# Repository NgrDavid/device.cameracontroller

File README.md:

## Harp Camera Trigger Control

This device allows to trigger up to 2 cameras at a predefined frequency pulse or 2 servo motors. Connect cameras to CAM0 TRIG and CAM1 TRIG ports.

### Key Features ###

* Separate sample frequency for each camera
* Alternate between camera triggering and servo motor control
* Each camera output can be handled as pure digital output

### Connectivity ###

* 1x clock sync input (CLKIN) [stereo jack]
* 1x USB (for computer) [USB type B]
* 1x 5V supply out [screw terminal]
* 4x digital outputs (I/O interface for 2 cameras): CAM0 TRIG, CAM0 SYNC, CAM1 TRIG, CAM1 SYNC [screw terminal]
* 1x digital input for general purpose or camera control (IN0) [BNC]

## Interface ##

The interface with the Harp board can be done through [Bonsai](https://bonsai-rx.org/) or a dedicated GUI (Graphical User Interface).

In order to use this GUI, there are some software that needs to be installed:

1 - Install the [drivers](https://bitbucket.org/fchampalimaud/downloads/downloads/UsbDriver-2.12.26.zip).

2 - Install the [runtime](https://bitbucket.org/fchampalimaud/downloads/downloads/Runtime-1.0.zip).

3 - Reboot the computer.

4 - Install the [GUI](https://bitbucket.org/fchampalimaud/downloads/downloads/Harp%20Camera%20Controller%20v1.0.1.zip).

## Licensing ##

Each subdirectory will contain a license or, possibly, a set of licenses if it involves both hardware and software.

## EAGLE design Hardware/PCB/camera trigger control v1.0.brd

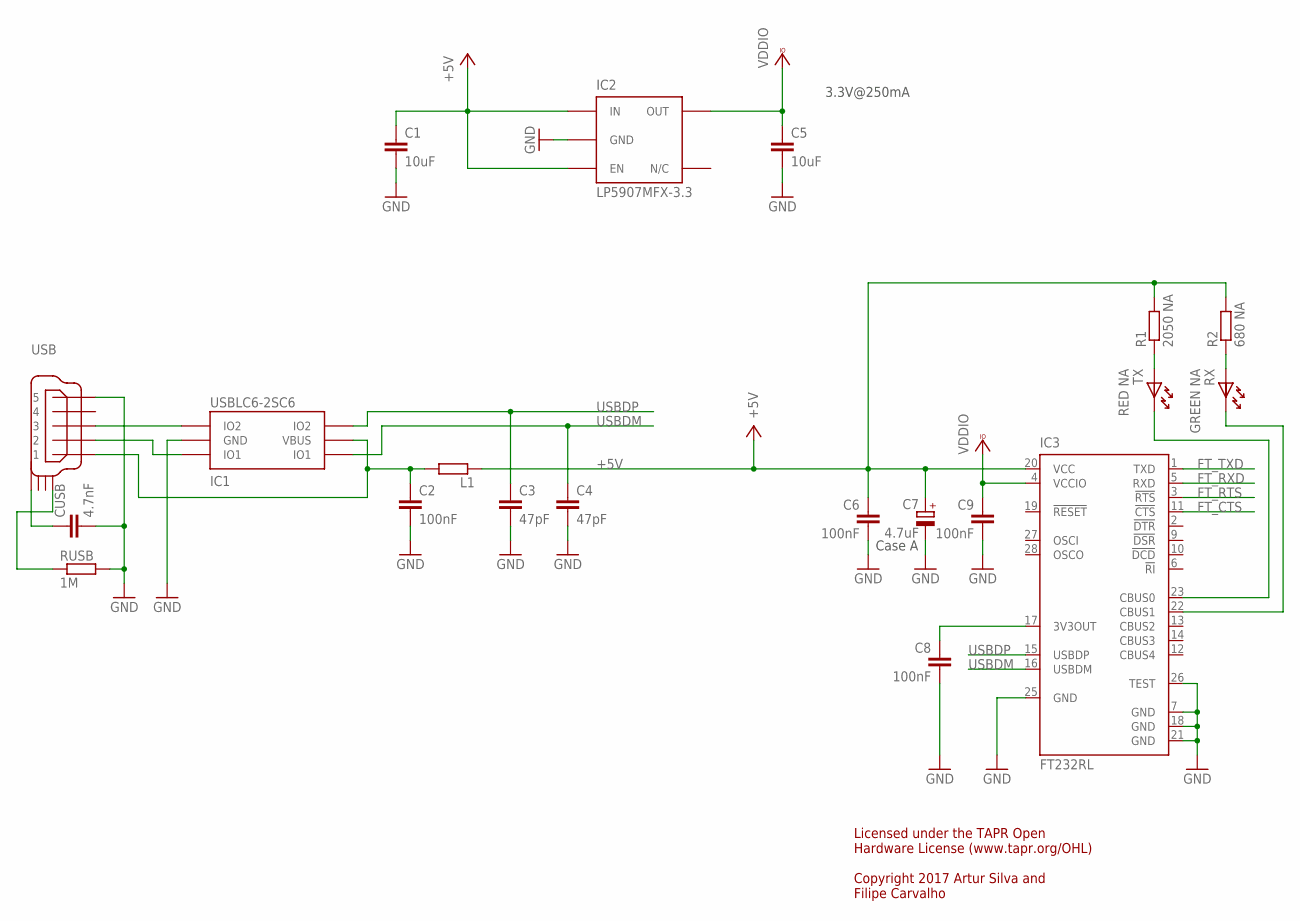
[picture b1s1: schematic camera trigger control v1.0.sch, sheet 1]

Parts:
C1, C5: 10uF; C0603
C2, C6, C8, C9: 100nF; C0402
C3, C4: 47pF; C0402
C7: 4.7uF; A/3216-18W
CUSB: 4.7nF; C0402
IC1: USBLC6-2SC6; SOT23-6L
IC2: LP5907MFX-3.3; TSOT23-5
IC3: FT232RL; SSOP28
L1: ???; R0805
R1: 2050 NA; R0402
R2: 680 NA; R0402
RUSB: 1M; R0402
RX: GREEN NA; LED_HAND
TX: RED NA; LED_HAND
USB: USB_MINI_B; 240-0002-1

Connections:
+5V: C1.1, C6.1, C7.+, IC2.1 (IN), IC2.3 (EN), IC3.20 (VCC), L1.1, R1.2, R2.2; also elsewhere on the board
FT_CTS: IC3.11 (!CTS); also elsewhere on the board
FT_RTS: IC3.3 (!RTS); also elsewhere on the board
FT_RXD: IC3.5 (RXD); also elsewhere on the board
FT_TXD: IC3.1 (TXD); also elsewhere on the board
GND: C1.2, C2.2, C3.2, C4.2, C5.2, C6.2, C7.-, C8.2, C9.2, CUSB.2, IC1.P$2 (GND), IC2.2 (GND), IC3.7 (GND), IC3.18 (GND), IC3.21 (GND), IC3.25 (GND), IC3.26 (TEST), RUSB.2, USB.P$5 (5); also elsewhere on the board
unnamed: C8.1, IC3.17 (3V3OUT)
unnamed: C2.1, IC1.P$5 (VBUS), L1.2, USB.P$1 (1)
unnamed: IC1.P$1 (IO1), USB.P$2 (2)
unnamed: R2.1, RX.A
unnamed: IC3.23 (CBUS0), TX.K
unnamed: IC3.22 (CBUS1), RX.K
unnamed: IC1.P$3 (IO2), USB.P$3 (3)
unnamed: CUSB.1, USB.SHIELD_4
unnamed: RUSB.1, USB.SHIELD_1
unnamed: R1.1, TX.A
USBDM: C4.1, IC1.P$6 (IO1), IC3.16 (USBDM)
USBDP: C3.1, IC1.P$4 (IO2), IC3.15 (USBDP)
VCCIO: C5.1, C9.1, IC2.5 (OUT), IC3.4 (VCCIO); also elsewhere on the board

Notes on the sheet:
Case A
3.3V@250mA
Licensed under the TAPR Open Hardware License (www.tapr.org/OHL) Copyright 2017 Artur Silva and Filipe Carvalho

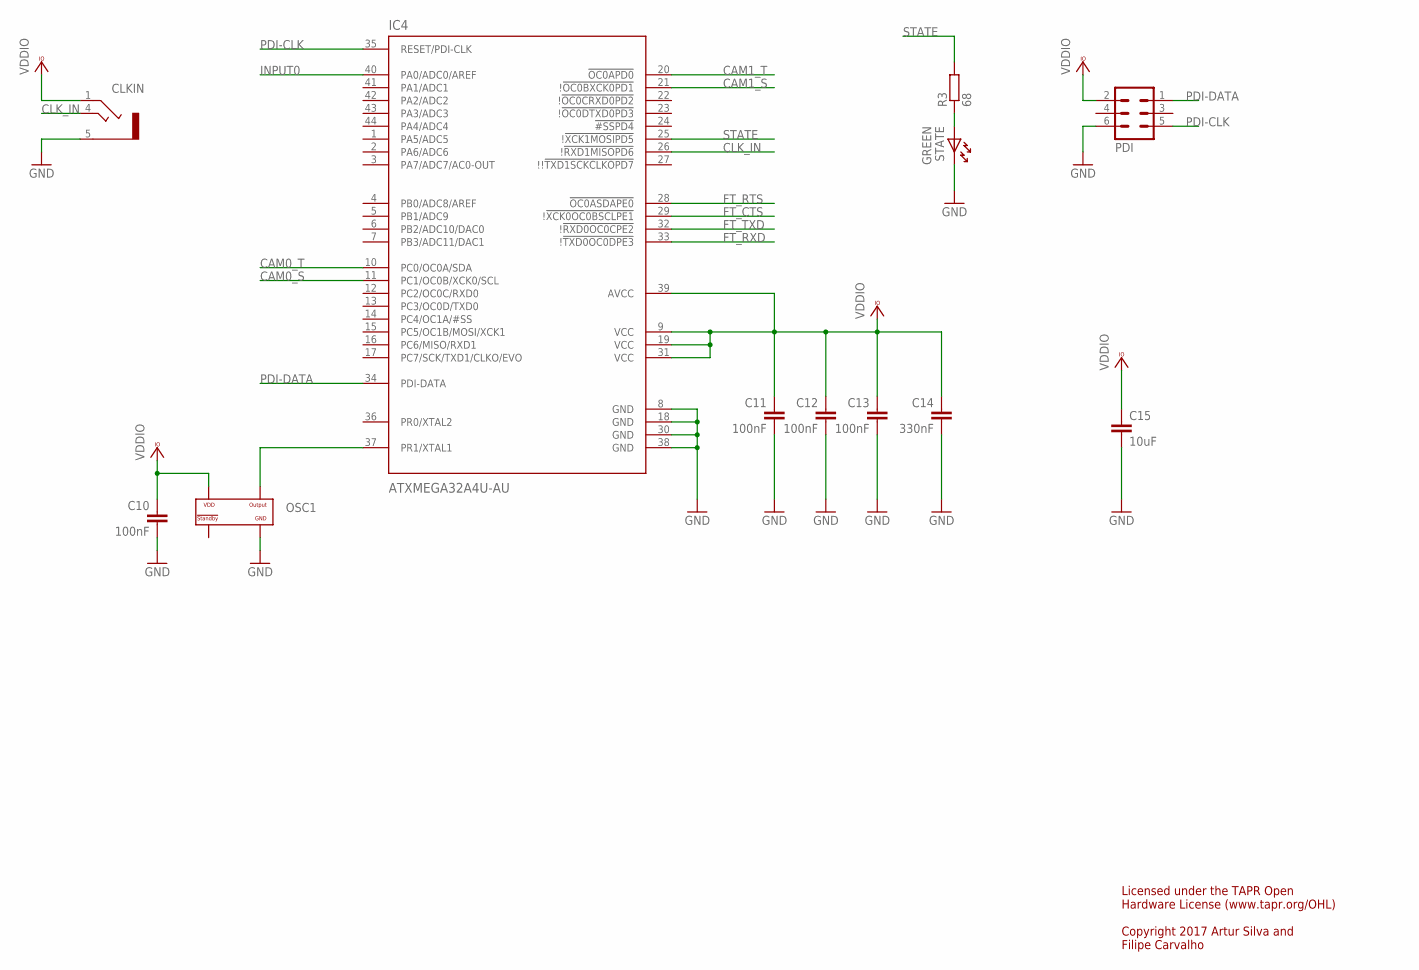
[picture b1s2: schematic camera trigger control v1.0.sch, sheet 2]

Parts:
C10, C11, C12, C13: 100nF; C0402
C14: 330nF; C0402
C15: 10uF; C0603
CLKIN: STEREO_JACK; 35RASMT2BHNTRX
IC4: ATXMEGA32A4U-AU; QFP80P1200X1200X120-44N
OSC1: OSCILLATOR; OSCILLATOR_3.2X2.5
PDI: MA03-2
R3: 68; R0402
STATE: GREEN; LED_HAND

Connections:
CAM0_S: IC4.11 (PC1/OC0B/XCK0/SCL); also elsewhere on the board
CAM0_T: IC4.10 (PC0/OC0A/SDA); also elsewhere on the board
CAM1_S: IC4.21 (!!OC0BXCK0PD1); also elsewhere on the board
CAM1_T: IC4.20 (!OC0APD0); also elsewhere on the board
CLK_IN: CLKIN.4, IC4.26 (!!RXD1MISOPD6)
FT_CTS: IC4.29 (!!XCK0OC0BSCLPE1); also elsewhere on the board
FT_RTS: IC4.28 (!OC0ASDAPE0); also elsewhere on the board
FT_RXD: IC4.33 (!!TXD0OC0DPE3); also elsewhere on the board
FT_TXD: IC4.32 (!!RXD0OC0CPE2); also elsewhere on the board
GND: C10.2, C11.2, C12.2, C13.2, C14.2, C15.2, CLKIN.5, IC4.8 (GND), IC4.18 (GND), IC4.30 (GND), IC4.38 (GND), OSC1.P$2 (GND), PDI.6, STATE.K; also elsewhere on the board
INPUT0: IC4.40 (PA0/ADC0/AREF); also elsewhere on the board
unnamed: R3.1, STATE.A
OSC1: IC4.37 (PR1/XTAL1), OSC1.P$3 (OUTPUT)
PDI-CLK: IC4.35 (RESET/PDI-CLK), PDI.5
PDI-DATA: IC4.34 (PDI-DATA), PDI.1
STATE: IC4.25 (!!XCK1MOSIPD5), R3.2
VCCIO: C10.1, C11.1, C12.1, C13.1, C14.1, C15.1, CLKIN.1, IC4.9 (VCC), IC4.19 (VCC), IC4.31 (VCC), IC4.39 (AVCC), OSC1.P$4 (VDD), PDI.2; also elsewhere on the board

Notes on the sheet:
Licensed under the TAPR Open Hardware License (www.tapr.org/OHL) Copyright 2017 Artur Silva and Filipe Carvalho

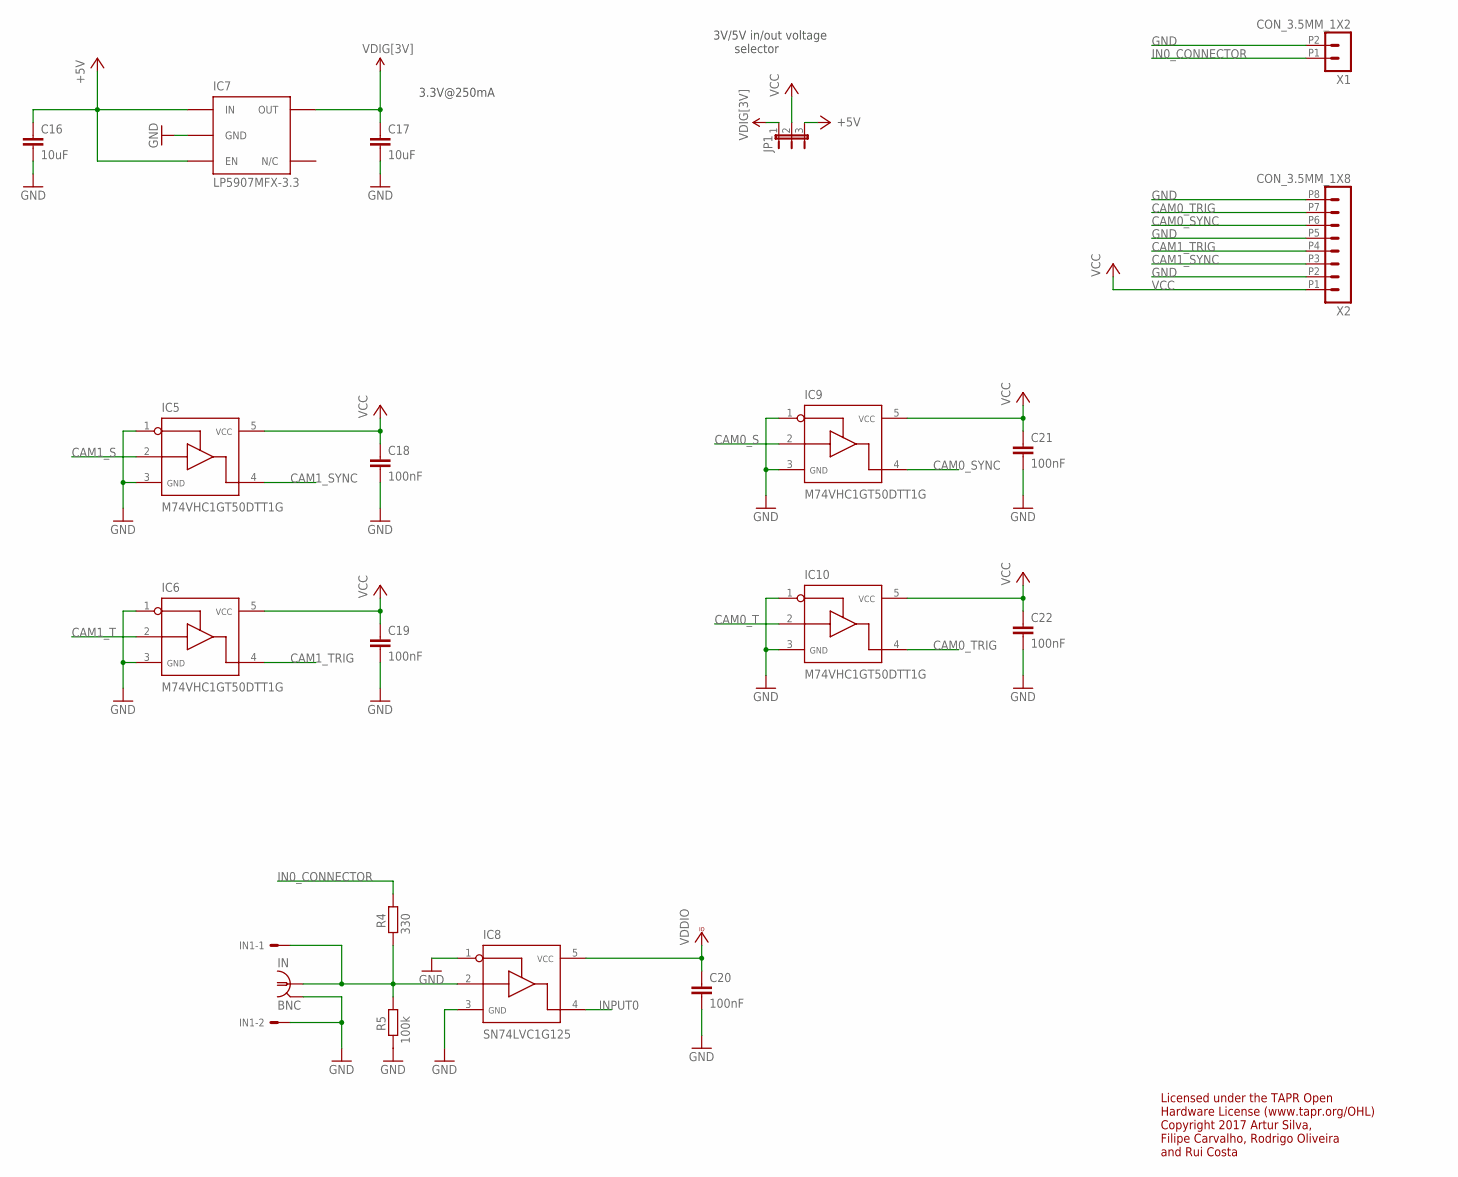
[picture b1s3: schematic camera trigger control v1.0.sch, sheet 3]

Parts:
C16, C17: 10uF; C0603
C18, C19, C20, C21, C22: 100nF; C0402
IC5, IC6, IC9, IC10: M74VHC1GT50DTT1G; SOT23-5
IC7: LP5907MFX-3.3; TSOT23-5
IC8: SN74LVC1G125; SOT23-5
IN: BNC; BNC_RA
IN1: 22-05-7028-02; 7395-02
JP1: JP2E; JP2
R4: 330; R0402
R5: 100k; R0402
X1: CON_3.5MM_1X2
X2: CON_3.5MM_1X8

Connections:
+5V: C16.1, IC7.1 (IN), IC7.3 (EN), JP1.3; also elsewhere on the board
CAM0_S: IC9.2; also elsewhere on the board
CAM0_SYNC: IC9.4, X2.P6 (6)
CAM0_T: IC10.2; also elsewhere on the board
CAM0_TRIG: IC10.4, X2.P7 (7)
CAM1_S: IC5.2; also elsewhere on the board
CAM1_SYNC: IC5.4, X2.P3 (3)
CAM1_T: IC6.2; also elsewhere on the board
CAM1_TRIG: IC6.4, X2.P4 (4)
GND: C16.2, C17.2, C18.2, C19.2, C20.2, C21.2, C22.2, IC5.1, IC5.3, IC6.1, IC6.3, IC7.2 (GND), IC8.1, IC8.3, IC9.1, IC9.3, IC10.1, IC10.3, IN.2, IN1.2, R5.2, X1.P2 (2), X2.P2 (2), X2.P5 (5), X2.P8 (8); also elsewhere on the board
IN0: IC8.2, IN.1, IN1.1, R4.2, R5.1
IN0_CONNECTOR: R4.1, X1.P1 (1)
INPUT0: IC8.4; also elsewhere on the board
VCC: C18.1, C19.1, C21.1, C22.1, IC5.5, IC6.5, IC9.5, IC10.5, JP1.2, X2.P1 (1)
VCCIO: C20.1, IC8.5; also elsewhere on the board
VDIG[3V]: C17.1, IC7.5 (OUT), JP1.1

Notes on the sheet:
3.3V@250mA
3V/5V in/out voltage selector
Licensed under the TAPR Open Hardware License (www.tapr.org/OHL) Copyright 2017 Artur Silva, Filipe Carvalho, Rodrigo Oliveira and Rui Costa

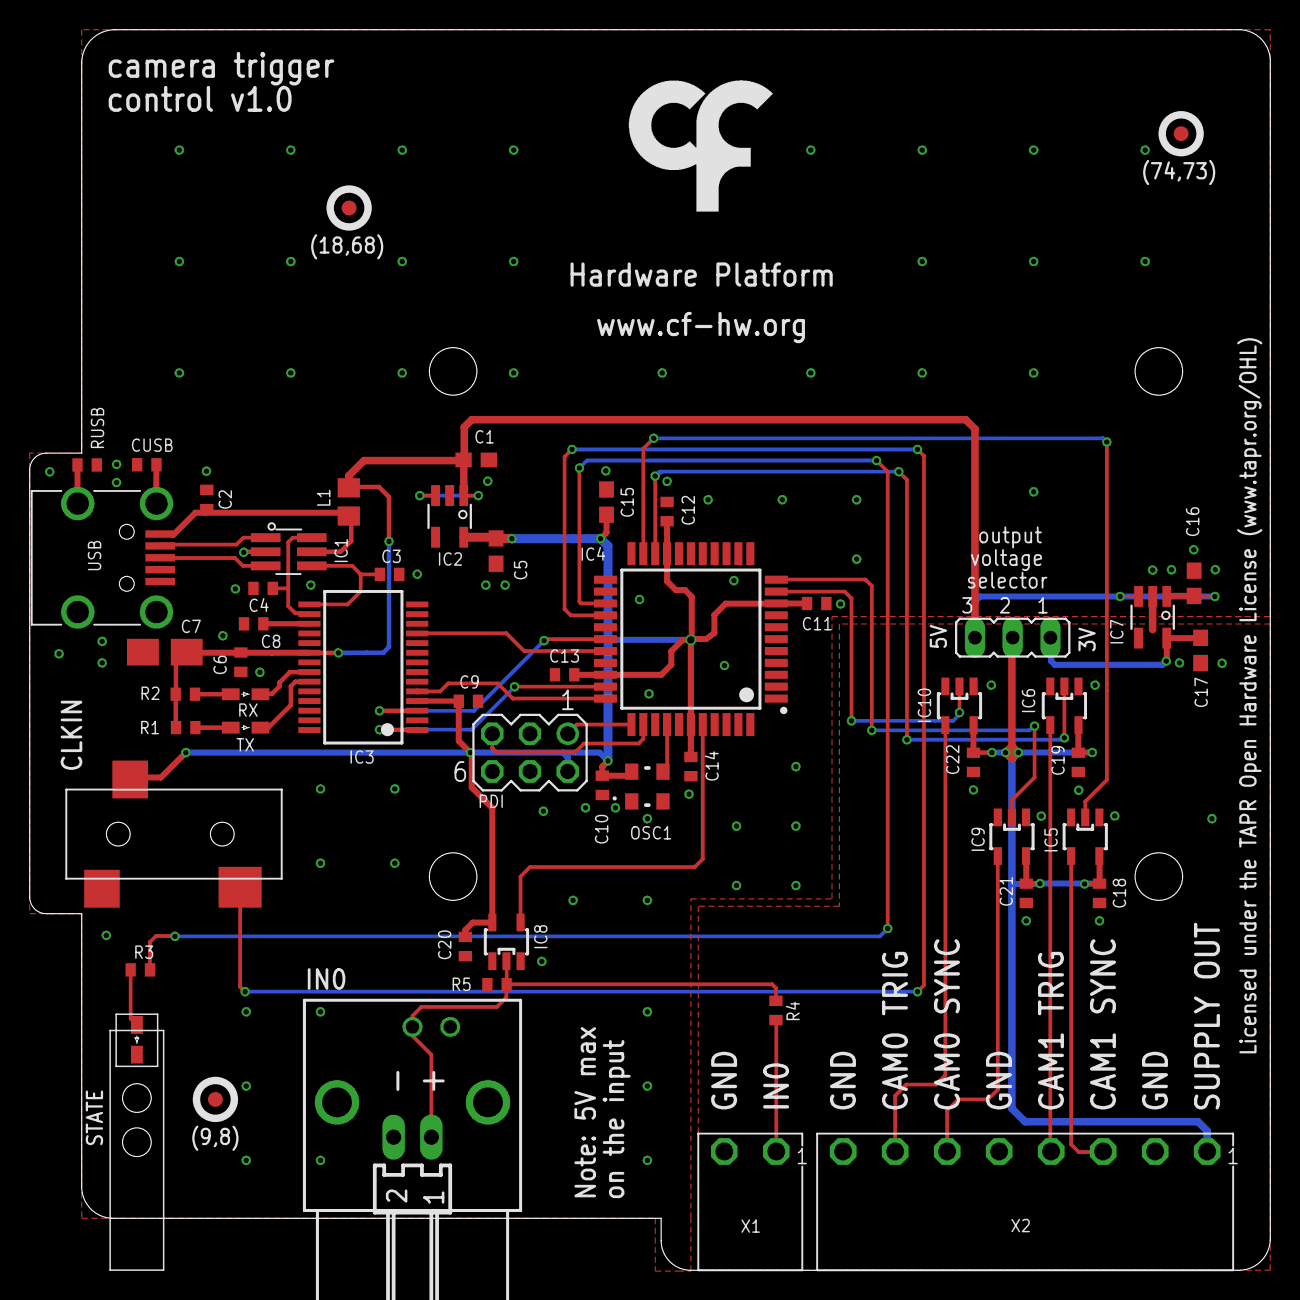
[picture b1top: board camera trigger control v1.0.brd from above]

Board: 2 copper layers, 83.5 x 83.5 mm, 57 parts (0 on the bottom side), 38 nets.

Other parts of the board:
U$1: LED_PIPE_7513D2-L
U$4, U$5, U$6: FIDUCIAL
U$9: LOGO_6

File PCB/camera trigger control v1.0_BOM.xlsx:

| Part(s) | Quantity | Description | Distributor | Part. No.
 | IC1 | 1 | ESD Protection Low Cap | Mouser | 511-USBLC6-2SC6
 | IC2, IC7 | 2 | LDO 250mA Ultra-Lo Noise LDO Reg | Mouser | 595-LP5907MFX-3.3NPB
 | IC3 | 1 | IC USB USB to Serial UART Enhanced IC SSOP-28 | Mouser | 895-FT232RL
 | IC4 | 1 | ATXMEGA64A4U-AU, ATxmega, 32 MHz, 64 KB, 4 KB, 44, TQFP | Mouser | 556-ATXMEGA64A4U-AU
 | IC5, IC6, IC9, IC10 | 4 | Buffers e line drivers 1.65-5.5V Single Non-Inverting TTL | Mouser | 863-M74VHC1GT50DTT1G
 | IC8 | 1 | SingleBuffer / Driver, 1.65V to 5.5V, SOT-23-5 | Mouser | 595-SN74LVC1G125DBVR
 | C3, C4 | 2 | CAP CER 47pF 50V ±5% C0G 0402 | Mouser | 77-VJ0402A470JXACBC
 | CUSB | 1 | CAP CER 4.7nF 100V ±10% X7R 0402 | Mouser | 81-GRM155R72A472KA01
 | C2, C6, C8, C9, C10, C11, C12, C13, C18, C19, C20, C21, C22 | 13 | CAP CER 100nF 10V X5R 0402 | REEL | REEL
 | C14 | 1 | CAP CER 0.33uF 10V ±10% X5R 0402 | Mouser | GRM155R61A334KE15D
 | C7 | 1 | CAP TAN 4.7uF 6.3V ±10% 1206 | Mouser | 80-T491A475K006
 | C1, C5, C15, C16, C17 | 5 | CAP CER 10uF 10V ±10% X5R 0603 | Mouser | 81-GRM188R61A106KE9D
 | R1, R2 | 0 | DNI | DNI | DNI
 | R3 | 1 | RES SMD 68Ω OHM 5% 0402 | Mouser | 71-CRCW0402-68-E3
 | R4 | 1 | RES SMD 330Ω OHM 1% 0402 | Mouser | 667-ERJ-PA2F3300X
 | R5 | 1 | RES SMD 100kΩ 1% 0402 | REEL | REEL
 | RUSB | 1 | RES SMD 1MΩ 1% 0402 | Mouser | 652-CR0402FX-1004GLF
 | L1 | 1 | 40ohms 100MHz 1.5A Monolithic 0805 SMD | Mouser | 875-MI0805K400R-10
 | STATE | 1 | LED, Green, 1.6mm x 0.8mm, 566 nm, 2.1 V, 20 mA, 15 mcd | Mouser | 78-TLMP1100-GS08
 | RX, TX | 0 | DNI | DNI | DNI
 | OSC1 | 1 | 32MHz 10ppm | Mouser | 998-1001CI5032.0000T
 | PDI | 1 | 6P DR UNSHRD HRD | Mouser | 649-67996-206HLF
 | JP1 | 1 | 3POS Gold Male | Mouser | 649-68001-203HLF
 |  | 1 | SHUNT JUMPER, 2POS | Farnell | 2396301
 | USB | 1 | UX60-MB-5S8 | Mouser | 798-UX60-MB-5S8
 | USB Cable | 1 | USB A - MINI-B 0.8M - MINI-B 0.8M BLACK | Mouser | 538-88732-8502
 | IN0 | 1 | R.A. JACK 50 OHM | Mouser | 571-5227161-1
 | CLKIN | 1 | SMT 3.5 STEREO REEL | Mouser | 502-35RASMT2BHNTRX
 |  | 1 | Tubos de Luz LED CML LIGHTPIPE | Mouser | 606-7513D2-L
 |  | 1 | IMO 20.1550M/8-E Pluggable Terminal Block, 3.5 mm, 8 Ways | Farnell | 2575220
 |  | 1 | IMO 20.1550M/2-E Pluggable Terminal Block, 3.5 mm, 2 Ways | Farnell | 2575215
 | X1 | 1 | Horizontal, Header, 3.5 mm, 2 Ways, 10 A, 250 V, Through Hole Right Angle | Farnell | 20.155MH/2-E
 | X2 | 1 | Horizontal, Header, 3.5 mm, 8 Ways, 10 A, 250 V, Through Hole Right Angle | Farnell | 20.155MH/8-E
 | Components | 52
 | Licensed under the TAPR Open Hardware License (www.tapr.org/OHL)
 | Copyright 2017 Artur Silva and Filipe Carvalho

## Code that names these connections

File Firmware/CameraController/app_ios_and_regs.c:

#include <avr/io.h>
#include "hwbp_core_types.h"
#include "app_ios_and_regs.h"

/************************************************************************/
/* Configure and initialize IOs                                         */
/************************************************************************/
void init_ios(void)
{	/* Configure input pins */
	io_pin2in(&PORTA, 0, PULL_IO_TRISTATE, SENSE_IO_EDGES_BOTH);         // INPUT0

	/* Configure input interrupts */
	io_set_int(&PORTA, INT_LEVEL_LOW, 0, (1<<0), false);                 // INPUT0

	/* Configure output pins */
	io_pin2out(&PORTC, 0, OUT_IO_DIGITAL, IN_EN_IO_EN);                  // CAM0_TRIG
	io_pin2out(&PORTC, 1, OUT_IO_DIGITAL, IN_EN_IO_EN);                  // CAM0_SYNC
	io_pin2out(&PORTD, 0, OUT_IO_DIGITAL, IN_EN_IO_EN);                  // CAM1_TRIG
	io_pin2out(&PORTD, 1, OUT_IO_DIGITAL, IN_EN_IO_EN);                  // CAM1_SYNC

	/* Initialize output pins */
	clr_CAM0_TRIG;
	clr_CAM0_SYNC;
	clr_CAM1_TRIG;
	clr_CAM1_SYNC;
}

/************************************************************************/
/* Registers' stuff                                                     */
/************************************************************************/
AppRegs app_regs;

uint8_t app_regs_type[] = {
	TYPE_U8,
	TYPE_U8,
	TYPE_U8,
	TYPE_U8,
	TYPE_U8,
	TYPE_U8,
	TYPE_U8,
	TYPE_U8,
	TYPE_U8,
	TYPE_U8,
	TYPE_U8,
	TYPE_U8,
	TYPE_U8,
	TYPE_U8,
	TYPE_U8,
	TYPE_U8,
	TYPE_U8,
	TYPE_U8,
	TYPE_U16,
	TYPE_U16,
	TYPE_U16,
	TYPE_U8,
	TYPE_U16,
	TYPE_U16,
	TYPE_U16,
	TYPE_U8,
	TYPE_U8,
	TYPE_U8
};

uint16_t app_regs_n_elements[] = {
	1,
	1,
	1,
	1,
	1,
	1,
	1,
	1,
	1,
	1,
	1,
	1,
	1,
	1,
	1,
	1,
	1,
	1,
	1,
	1,
	1,
	1,
	1,
	1,
	1,
	1,
	1,
	1
};

uint8_t *app_regs_pointer[] = {
	(uint8_t*)(&app_regs.REG_START_CAMS),
	(uint8_t*)(&app_regs.REG_STOP_CAMS),
	(uint8_t*)(&app_regs.REG_ENABLE_MOTORS),
	(uint8_t*)(&app_regs.REG_DISABLE_MOTORS),
	(uint8_t*)(&app_regs.REG_SET_OUTPUTS),
	(uint8_t*)(&app_regs.REG_CLR_OUTPUTS),
	(uint8_t*)(&app_regs.REG_OUTPUTS),
	(uint8_t*)(&app_regs.REG_INPUT0),
	(uint8_t*)(&app_regs.REG_CAM0),
	(uint8_t*)(&app_regs.REG_CAM1),
	(uint8_t*)(&app_regs.REG_SYNC0),
	(uint8_t*)(&app_regs.REG_SYNC1),
	(uint8_t*)(&app_regs.REG_MOTORS_STATE),
	(uint8_t*)(&app_regs.REG_RESERVED0),
	(uint8_t*)(&app_regs.REG_SYNC_INTERVAL),
	(uint8_t*)(&app_regs.REG_RESERVED1),
	(uint8_t*)(&app_regs.REG_IN0_MODE),
	(uint8_t*)(&app_regs.REG_CAM0_MODE),
	(uint8_t*)(&app_regs.REG_CAM0_FREQ),
	(uint8_t*)(&app_regs.REG_CAM0_MMODE_PERIOD),
	(uint8_t*)(&app_regs.REG_CAM0_MMODE_PULSE),
	(uint8_t*)(&app_regs.REG_CAM1_MODE),
	(uint8_t*)(&app_regs.REG_CAM1_FREQ),
	(uint8_t*)(&app_regs.REG_CAM1_MMODE_PERIOD),
	(uint8_t*)(&app_regs.REG_CAM1_MMODE_PULSE),
	(uint8_t*)(&app_regs.REG_RESERVED2),
	(uint8_t*)(&app_regs.REG_RESERVED3),
	(uint8_t*)(&app_regs.REG_EVT_EN)
};

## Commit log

2017-09-29 README.md created online with Bitbucket
2017-09-29 Added first files.
2017-09-29 Updated project for the right optimization (-O3).
2017-10-02 Update registers.xls to final list.
2017-10-02 All registers and features were implemented (not tested yet).
2017-10-02 Update Events Enable register to U8.
2017-10-02 Corrected several bugs and small updates on the registers.xls file.
2017-10-02 Updated bitmask of register OUTPUTS.
2017-10-02 Added a new feature that stops the current behavior when goes into Standby Mode.
2017-10-02 Removed some compiler warnings.
2017-10-06 Added ability to start camera imeddiatly after receive the IN0 trigger.
2017-10-12 Updated code to be able to set the outputs accordingly the saved configuration.
2017-10-12 Added a new feature that allows the motor to start immediatly depending on the IN0 state and IN0 configuration.
2018-01-15 Updated to Harp version 1.1.
2018-01-23 Updated to Harp version 1.2.
2018-01-30 Updated to Harp version 1.3.
2018-03-04 Increased lower limit of the camera frequency to 2 Hz (1 Hz was not working properly).
2018-03-14 Corrected issue: when stopping the camera triggering, the last pulse was not correct.
2018-03-14 Updated to Harp version 1.4.
2018-03-14 Increased firmware version to 1.1.
2022-12-16 Add PCB and BOM files
2022-12-16 Add licenses
2022-12-18 Correct picture transparency
2022-12-18 refactor assets' folder structure
2022-12-20 fix typo
2022-12-23 refactor repository structure
2023-08-18 Add firmware gitignore
2023-08-18 Remove extension
2023-08-18 Add interface generators
2023-08-18 First draft of schema
2023-08-18 Add punctuation
2023-08-18 Format description as string to escape ","
2023-08-18 Add Interfaces
2023-08-19 Correct minor typos
2023-08-20 Update PCB image asset
2023-08-20 Add HW .gitignore
2023-08-20 Add Mechanical folder and license
2023-08-22 Change start core parameters
2023-08-23 Update .cppproj library path
2023-08-23 Remove atmel studio v6.2 old files
2024-07-24 Update yml
2024-07-24 Update autogen interface
2024-07-24 Autoformat csproj
2024-11-13 Update device schema source
2024-11-13 Update package metadata and add library package
2024-11-13 Update generators and regenerate interface
2025-05-16 Create basic CI/CD for interface package
